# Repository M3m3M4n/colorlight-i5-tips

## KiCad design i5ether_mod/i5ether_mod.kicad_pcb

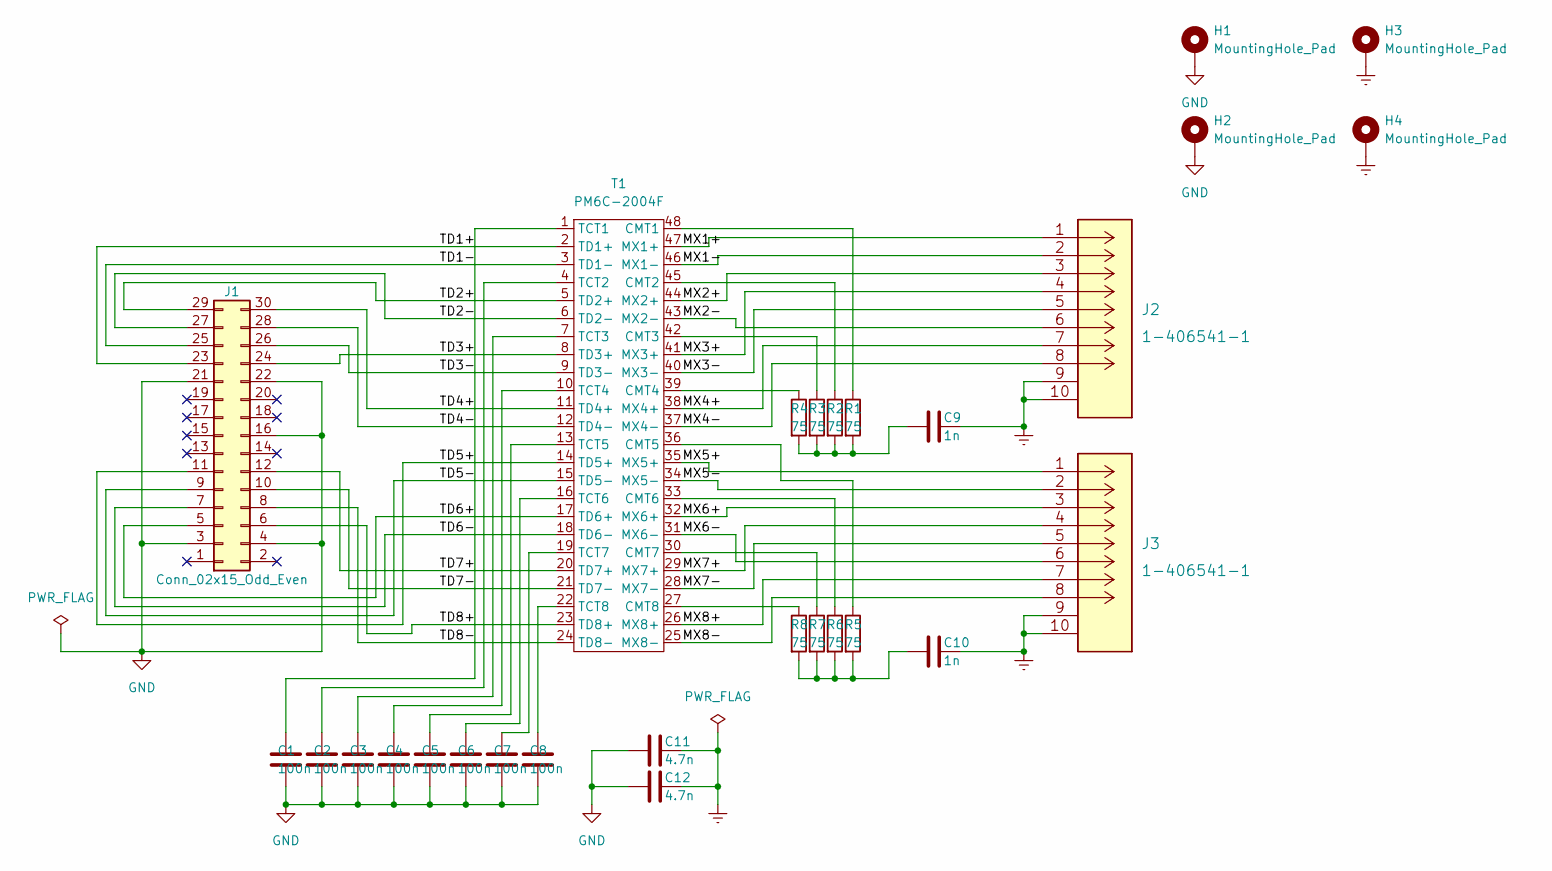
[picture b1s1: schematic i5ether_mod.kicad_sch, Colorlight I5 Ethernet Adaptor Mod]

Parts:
C1, C2, C3, C4, C5, C6, C7, C8: 100n; C_0805_2012Metric_Pad1.18x1.45mm_HandSolder
C9, C10: 1n; C_0805_2012Metric_Pad1.18x1.45mm_HandSolder
C11, C12: 4.7n; C_1812_4532Metric_Pad1.57x3.40mm_HandSolder
H1, H2, H3, H4: MountingHole_Pad; MountingHole_3.2mm_M3_Pad
J1: Conn_02x15_Odd_Even; PinHeader_2x15_P2.54mm_Horizontal
J2, J3: 1-406541-1
R1, R2, R3, R4, R5, R6, R7, R8: 75; R_0805_2012Metric_Pad1.20x1.40mm_HandSolder
T1: PM6C-2004F; PM6C-2004F_SOP48

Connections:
/MX1+: J2.1, T1.47 (MX1+)
/MX1-: J2.2, T1.46 (MX1-)
/MX2+: J2.3, T1.44 (MX2+)
/MX2-: J2.6, T1.43 (MX2-)
/MX3+: J2.4, T1.41 (MX3+)
/MX3-: J2.5, T1.40 (MX3-)
/MX4+: J2.7, T1.38 (MX4+)
/MX4-: J2.8, T1.37 (MX4-)
/MX5+: J3.1, T1.35 (MX5+)
/MX5-: J3.2, T1.34 (MX5-)
/MX6+: J3.3, T1.32 (MX6+)
/MX6-: J3.6, T1.31 (MX6-)
/MX7+: J3.4, T1.29 (MX7+)
/MX7-: J3.5, T1.28 (MX7-)
/MX8+: J3.7, T1.26 (MX8+)
/MX8-: J3.8, T1.25 (MX8-)
/TD1+: J1.23, T1.2 (TD1+)
/TD1-: J1.25, T1.3 (TD1-)
/TD2+: J1.29, T1.5 (TD2+)
/TD2-: J1.27, T1.6 (TD2-)
/TD3+: J1.24, T1.8 (TD3+)
/TD3-: J1.26, T1.9 (TD3-)
/TD4+: J1.30, T1.11 (TD4+)
/TD4-: J1.28, T1.12 (TD4-)
/TD5+: J1.11, T1.14 (TD5+)
/TD5-: J1.9, T1.15 (TD5-)
/TD6+: J1.5, T1.17 (TD6+)
/TD6-: J1.7, T1.18 (TD6-)
/TD7+: J1.12, T1.20 (TD7+)
/TD7-: J1.10, T1.21 (TD7-)
/TD8+: J1.6, T1.23 (TD8+)
/TD8-: J1.8, T1.24 (TD8-)
Earth: C9.1, C10.1, C11.1, C12.1, H3.1, H4.1, J2.9 (SHIELD), J2.10 (SHIELD), J3.9 (SHIELD), J3.10 (SHIELD)
GND: C1.2, C2.2, C3.2, C4.2, C5.2, C6.2, C7.2, C8.2, C11.2, C12.2, H1.1, H2.1, J1.3, J1.4, J1.16, J1.21, J1.22
unnamed: C1.1, T1.1 (TCT1)
unnamed: C2.1, T1.4 (TCT2)
unnamed: C3.1, T1.7 (TCT3)
unnamed: C4.1, T1.10 (TCT4)
unnamed: C5.1, T1.13 (TCT5)
unnamed: C6.1, T1.16 (TCT6)
unnamed: C7.1, T1.19 (TCT7)
unnamed: C8.1, T1.22 (TCT8)
unnamed: C9.2, R1.2, R2.2, R3.2, R4.2
unnamed: C10.2, R5.2, R6.2, R7.2, R8.2
unnamed: R1.1, T1.48 (CMT1)
unnamed: R2.1, T1.45 (CMT2)
unnamed: R3.1, T1.42 (CMT3)
unnamed: R4.1, T1.39 (CMT4)
unnamed: R5.1, T1.36 (CMT5)
unnamed: R6.1, T1.33 (CMT6)
unnamed: R7.1, T1.30 (CMT7)
unnamed: R8.1, T1.27 (CMT8)

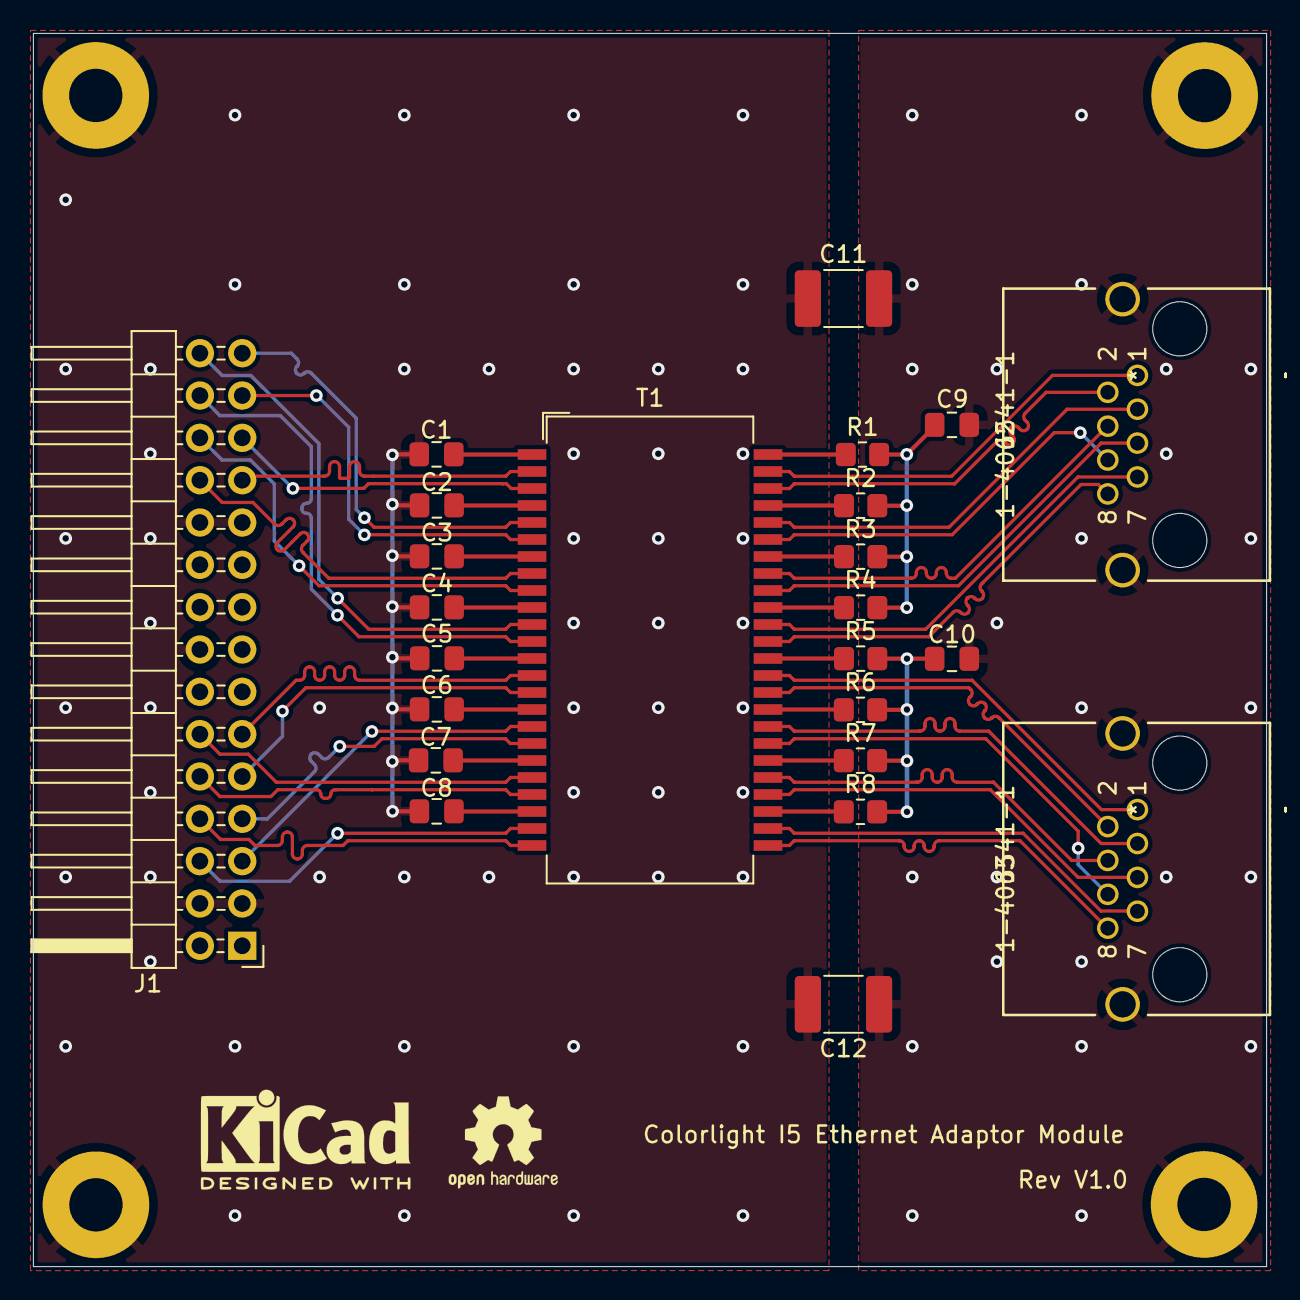
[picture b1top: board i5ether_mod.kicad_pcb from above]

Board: 2 copper layers, 74.0 x 74.0 mm, 28 parts (0 on the bottom side), 52 nets.

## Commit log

2022-01-11 change
2022-01-13 final
2022-01-13 gerbers

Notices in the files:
parts and their libraries:
Copyright 2016 Accelerated Designs. All rights reserved.
